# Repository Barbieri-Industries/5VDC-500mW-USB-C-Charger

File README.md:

# USB-C Charger (5VDC, 500mW)
---
A simple & compact USB-C Charger based on LM2596 Buck Regulator:
---
Input:
- 220VAC/60Hz from grid outlet

Output:
- 5VDC/500mW
---
Softwares:
- **KiCAD 10.0.0**
---
© 2026 Barbieri Industries. All rights reserved.

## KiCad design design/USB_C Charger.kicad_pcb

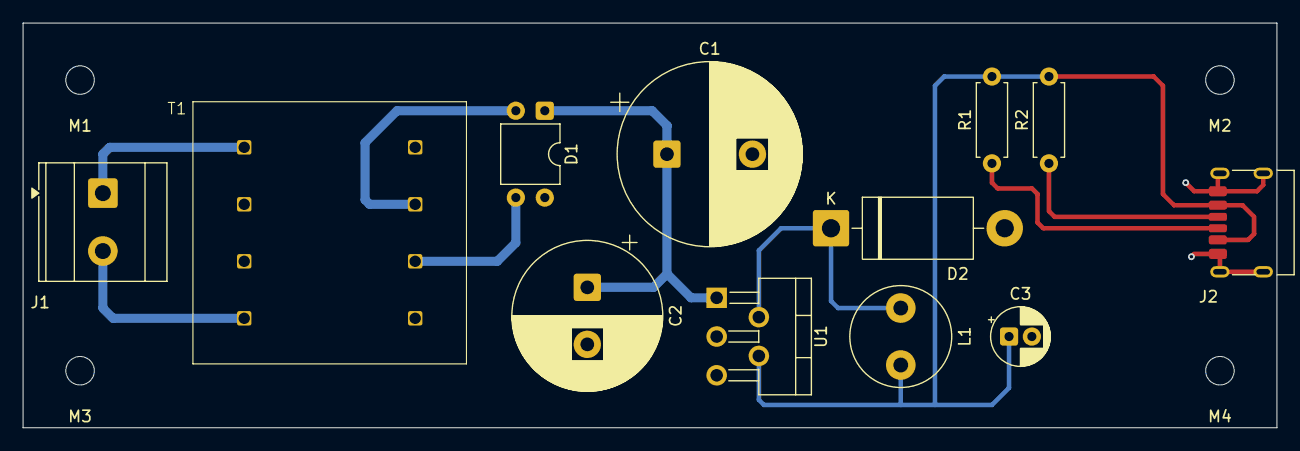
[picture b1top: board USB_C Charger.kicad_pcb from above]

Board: 2 copper layers, 110.0 x 35.5 mm, 16 parts (0 on the bottom side), 10 nets.

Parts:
C1: 1000uF; CP_Radial_D16.0mm_P7.50mm
C2: 680uF; CP_Radial_D13.0mm_P5.00mm
C3: 220uF; CP_Radial_D5.0mm_P2.00mm
D1: D_Bridge_+AA-; DIP-4_W7.62mm
D2: 1N5822; D_DO-201AD_P15.24mm_Horizontal
J1: AC INPUT; TerminalBlock_MetzConnect_Type073_RT02602HBLU_1x02_P5.08mm_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
J2: USB-C RECEPTACLE; USB_C_Receptacle_HRO_TYPE-C-31-M-17
L1: 33uH; L_Radial_D8.7mm_P5.00mm_Fastron_07HCP
M1, M2, M3, M4: MountingHole_2.5mm
R1, R2: 56kΩ; R_Axial_DIN0207_L6.3mm_D2.5mm_P7.62mm_Horizontal
T1: BV202S24006; Transformer_BV20_Series
U1: LM2596T-5; TO-220-5_P3.4x3.7mm_StaggerOdd_Lead3.8mm_Vertical

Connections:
+5VDC: C3.1, J2.A9 (VBUS), J2.B9 (VBUS), L1.2, R1.2, R2.2, U1.4 (FB)
+34VDC: C1.1, C2.1, D1.1 (+), U1.1 (VIN)
/SHEET 2/AC_GND: J1.2, T1.1 (AB)
/SHEET 2/AC_IN: J1.1, T1.4 (AA)
/SHEET 2/AC_OUT_1: D1.2, T1.6 (SB)
/SHEET 2/AC_OUT_2: D1.3, T1.7 (SA)
/SHEET 2/D2_L1: D2.1 (K), L1.1, U1.2 (OUT)
/SHEET 2/R1_J2_A5: J2.A5 (CC1), R1.1
/SHEET 2/R2_J2_B5: J2.B5 (CC2), R2.1
DC GND: C1.2, C2.2, C3.2, D1.4 (-), D2.2 (A), J2.A12 (GND), J2.B12 (GND), J2.SH (SHIELD), U1.3 (GND), U1.5 (~ON/OFF)
